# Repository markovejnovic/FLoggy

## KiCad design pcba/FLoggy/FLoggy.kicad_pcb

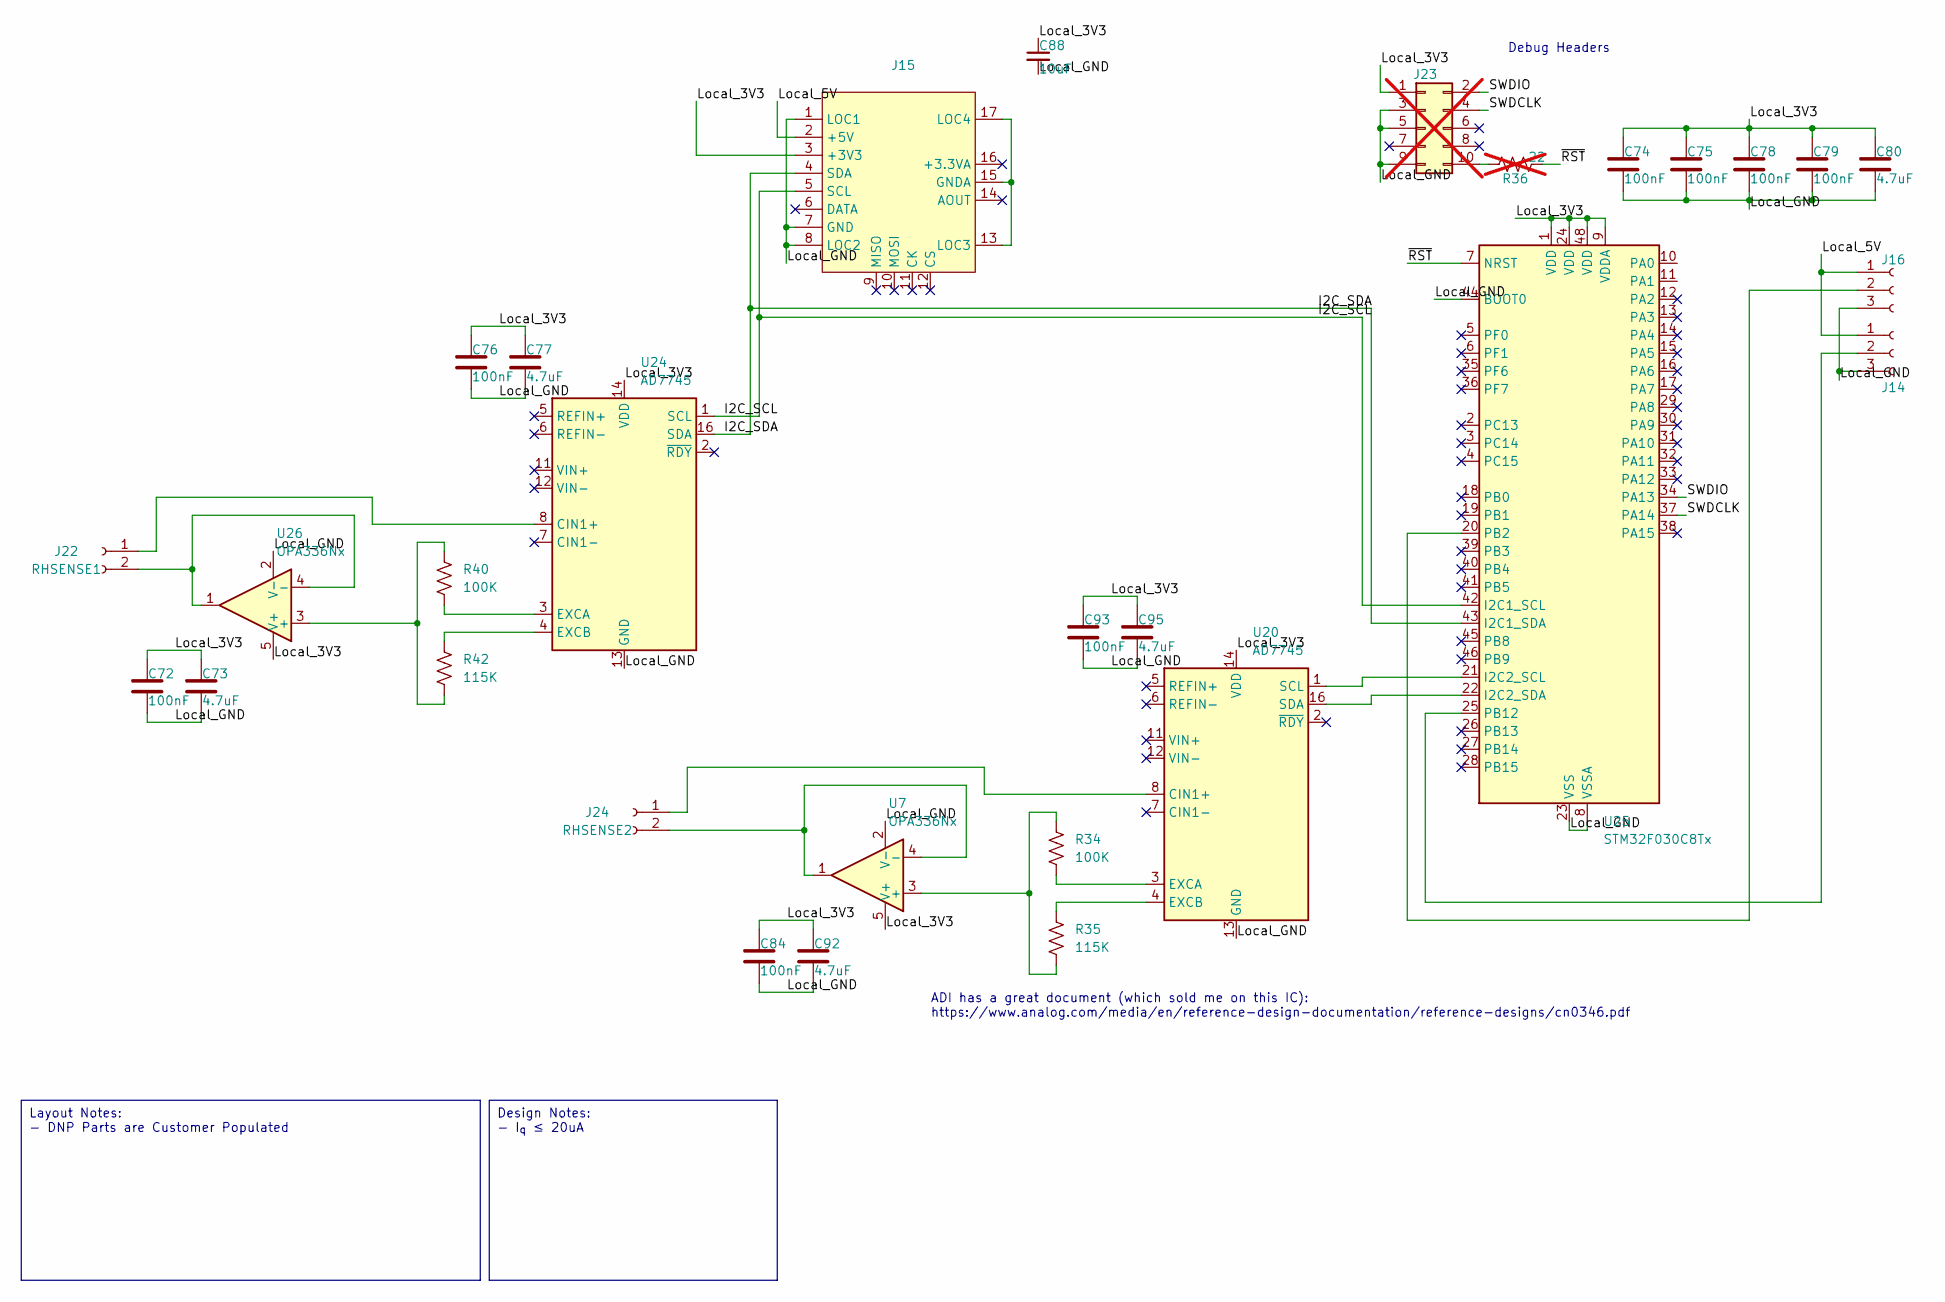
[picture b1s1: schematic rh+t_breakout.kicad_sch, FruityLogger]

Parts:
C72, C74, C75, C76, C78, C79, C84, C93: 100nF; C_0603_1608Metric; JLCPCB Basic? True
C73, C77, C80, C92, C95: 4.7uF; C_0805_2012Metric; JLCPCB Basic? True
C88: 10uF; C_0805_2012Metric; JLCPCB Basic? True
J14, J16: Conn_01x03_Socket; TerminalBlock_Phoenix_PT-1,5-3-3.5-H_1x03_P3.50mm_Horizontal
J15: FloggyModuleShield
J22: RHSENSE1; TerminalBlock_Phoenix_MPT-0,5-2-2.54_1x02_P2.54mm_Horizontal
J23: CTX_DBG; PinHeader_2x05_P1.27mm_Vertical_SMD; not fitted
J24: RHSENSE2; TerminalBlock_Phoenix_MPT-0,5-2-2.54_1x02_P2.54mm_Horizontal
R34, R40: 100K; R_0805_2012Metric; JLCPCB Basic? True
R35, R42: 115K; R_0603_1608Metric; JLCPCB Basic? False
R36: 22; R_0805_2012Metric; JLCPCB Basic? True; not fitted
U7, U26: OPA336Nx; SOT-23-5; JLCPCB Basic? False
U20, U24: AD7745; TSSOP-16_4.4x5mm_P0.65mm; JLCPCB Basic? False
U25: STM32F030C8Tx; LQFP-48_7x7mm_P0.5mm; JLCPCB Basic? True

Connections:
/RH + Temp Breakout 1/I2C_SCL: J15.5 (SCL), U24.1 (SCL), U25.42 (I2C1_SCL)
/RH + Temp Breakout 1/I2C_SDA: J15.4 (SDA), U24.16 (SDA), U25.43 (I2C1_SDA)
/RH + Temp Breakout 1/Local_3V3: C72.1, C73.1, C74.1, C75.1, C76.1, C77.1, C78.1, C79.1, C80.1, C84.1, C88.1, C92.1, C93.1, C95.1, J15.3 (+3V3), J23.1, U7.5 (V+), U20.14 (VDD), U24.14 (VDD), U25.1 (VDD), U25.9 (VDDA), U25.24 (VDD), U25.48 (VDD), U26.5 (V+)
/RH + Temp Breakout 1/Local_5V: J14.1, J15.2 (+5V), J16.1
/RH + Temp Breakout 1/Local_GND: C72.2, C73.2, C74.2, C75.2, C76.2, C77.2, C78.2, C79.2, C80.2, C84.2, C88.2, C92.2, C93.2, C95.2, J14.3, J15.1 (LOC1), J15.7 (GND), J15.8 (LOC2), J16.3, J23.3, J23.5, J23.9, U7.2 (V-), U20.13 (GND), U24.13 (GND), U25.8 (VSSA), U25.23 (VSS), U25.44 (BOOT0), U25.47 (VSS), U26.2 (V-)
/RH + Temp Breakout 1/SWDCLK: J23.4, U25.37 (PA14)
/RH + Temp Breakout 1/SWDIO: J23.2, U25.34 (PA13)
/RH + Temp Breakout 1/~RST: R36.2, U25.7 (NRST)
unnamed: J14.2, U25.25 (PB12)
unnamed: J15.13 (LOC3), J15.15 (GNDA), J15.17 (LOC4)
unnamed: J16.2, U25.20 (PB2)
unnamed: J22.1, U24.8 (CIN1+)
unnamed: J22.2, U26.1, U26.4 (-)
unnamed: J23.10, R36.1
unnamed: J24.1, U20.8 (CIN1+)
unnamed: J24.2, U7.1, U7.4 (-)
unnamed: R34.1, R35.2, U7.3 (+)
unnamed: R34.2, U20.3 (EXCA)
unnamed: R35.1, U20.4 (EXCB)
unnamed: U20.1 (SCL), U25.21 (I2C2_SCL)
unnamed: U20.16 (SDA), U25.22 (I2C2_SDA)
unnamed: R40.2, U24.3 (EXCA)
unnamed: R42.1, U24.4 (EXCB)
unnamed: R40.1, R42.2, U26.3 (+)

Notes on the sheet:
Design Notes: - I_{q} ≤ 20uA
Layout Notes: - DNP Parts are Customer Populated
Debug Headers
ADI has a great document (which sold me on this IC): https://www.analog.com/media/en/reference-design-documentation/reference-designs/cn0346.pdf

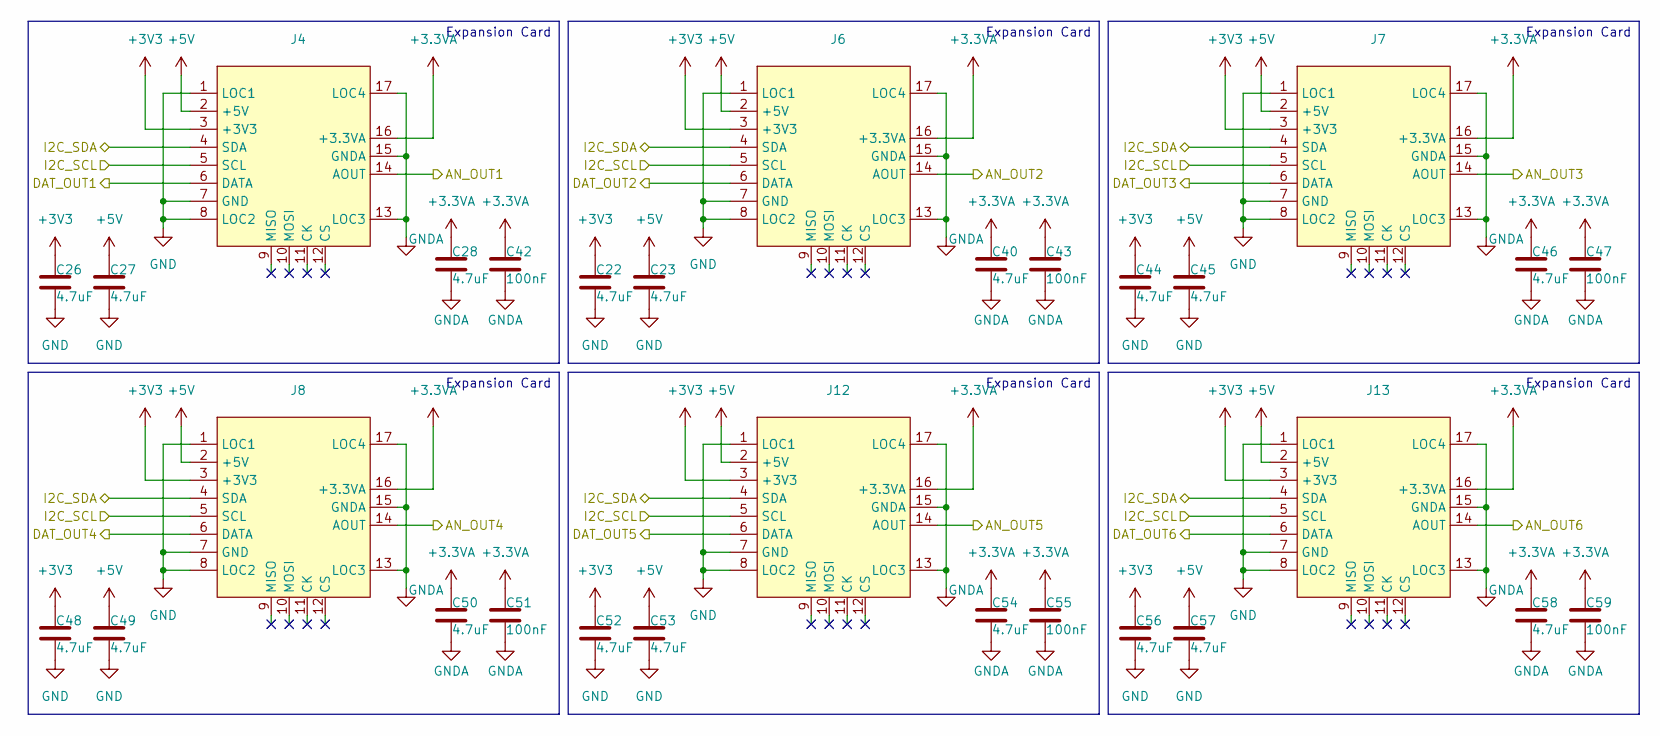
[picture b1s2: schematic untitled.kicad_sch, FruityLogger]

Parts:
C22, C23, C26, C27, C28, C40, C44, C45, C46, C48, C49, C50, C52, C53, C54, C56, C57, C58: 4.7uF; C_0805_2012Metric; JLCPCB Basic? True
C42, C43, C47, C51, C55, C59: 100nF; C_0603_1608Metric; JLCPCB Basic? True
J4, J6, J7, J8, J12, J13: FloggyModuleBase

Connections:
+3.3VA: C28.1, C40.1, C42.1, C43.1, C46.1, C47.1, C50.1, C51.1, C54.1, C55.1, C58.1, C59.1, J4.16 (+3.3VA), J6.16 (+3.3VA), J7.16 (+3.3VA), J8.16 (+3.3VA), J12.16 (+3.3VA), J13.16 (+3.3VA); also elsewhere on the board
+3V3: C22.1, C26.1, C44.1, C48.1, C52.1, C56.1, J4.3 (+3V3), J6.3 (+3V3), J7.3 (+3V3), J8.3 (+3V3), J12.3 (+3V3), J13.3 (+3V3); also elsewhere on the board
+5V: C23.1, C27.1, C45.1, C49.1, C53.1, C57.1, J4.2 (+5V), J6.2 (+5V), J7.2 (+5V), J8.2 (+5V), J12.2 (+5V), J13.2 (+5V); also elsewhere on the board
/MicroController/AIN1: J4.14 (AOUT); also elsewhere on the board
/MicroController/AIN2: J6.14 (AOUT); also elsewhere on the board
/MicroController/AIN3: J7.14 (AOUT); also elsewhere on the board
/MicroController/AIN4: J8.14 (AOUT); also elsewhere on the board
/MicroController/AIN5: J12.14 (AOUT); also elsewhere on the board
/MicroController/AIN6: J13.14 (AOUT); also elsewhere on the board
/MicroController/GPIO1: J4.6 (DATA); also elsewhere on the board
/MicroController/GPIO2: J6.6 (DATA); also elsewhere on the board
/MicroController/GPIO3: J7.6 (DATA); also elsewhere on the board
/MicroController/GPIO4: J8.6 (DATA); also elsewhere on the board
/MicroController/GPIO5: J12.6 (DATA); also elsewhere on the board
/MicroController/GPIO6: J13.6 (DATA); also elsewhere on the board
/MicroController/SCL: J4.5 (SCL), J6.5 (SCL), J7.5 (SCL), J8.5 (SCL), J12.5 (SCL), J13.5 (SCL); also elsewhere on the board
/MicroController/SDA: J4.4 (SDA), J6.4 (SDA), J7.4 (SDA), J8.4 (SDA), J12.4 (SDA), J13.4 (SDA); also elsewhere on the board
GND: C22.2, C23.2, C26.2, C27.2, C44.2, C45.2, C48.2, C49.2, C52.2, C53.2, C56.2, C57.2, J4.1 (LOC1), J4.7 (GND), J4.8 (LOC2), J6.1 (LOC1), J6.7 (GND), J6.8 (LOC2), J7.1 (LOC1), J7.7 (GND), J7.8 (LOC2), J8.1 (LOC1), J8.7 (GND), J8.8 (LOC2), J12.1 (LOC1), J12.7 (GND), J12.8 (LOC2), J13.1 (LOC1), J13.7 (GND), J13.8 (LOC2); also elsewhere on the board
GNDA: C28.2, C40.2, C42.2, C43.2, C46.2, C47.2, C50.2, C51.2, C54.2, C55.2, C58.2, C59.2, J4.13 (LOC3), J4.15 (GNDA), J4.17 (LOC4), J6.13 (LOC3), J6.15 (GNDA), J6.17 (LOC4), J7.13 (LOC3), J7.15 (GNDA), J7.17 (LOC4), J8.13 (LOC3), J8.15 (GNDA), J8.17 (LOC4), J12.13 (LOC3), J12.15 (GNDA), J12.17 (LOC4), J13.13 (LOC3), J13.15 (GNDA), J13.17 (LOC4); also elsewhere on the board

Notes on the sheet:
Expansion Card

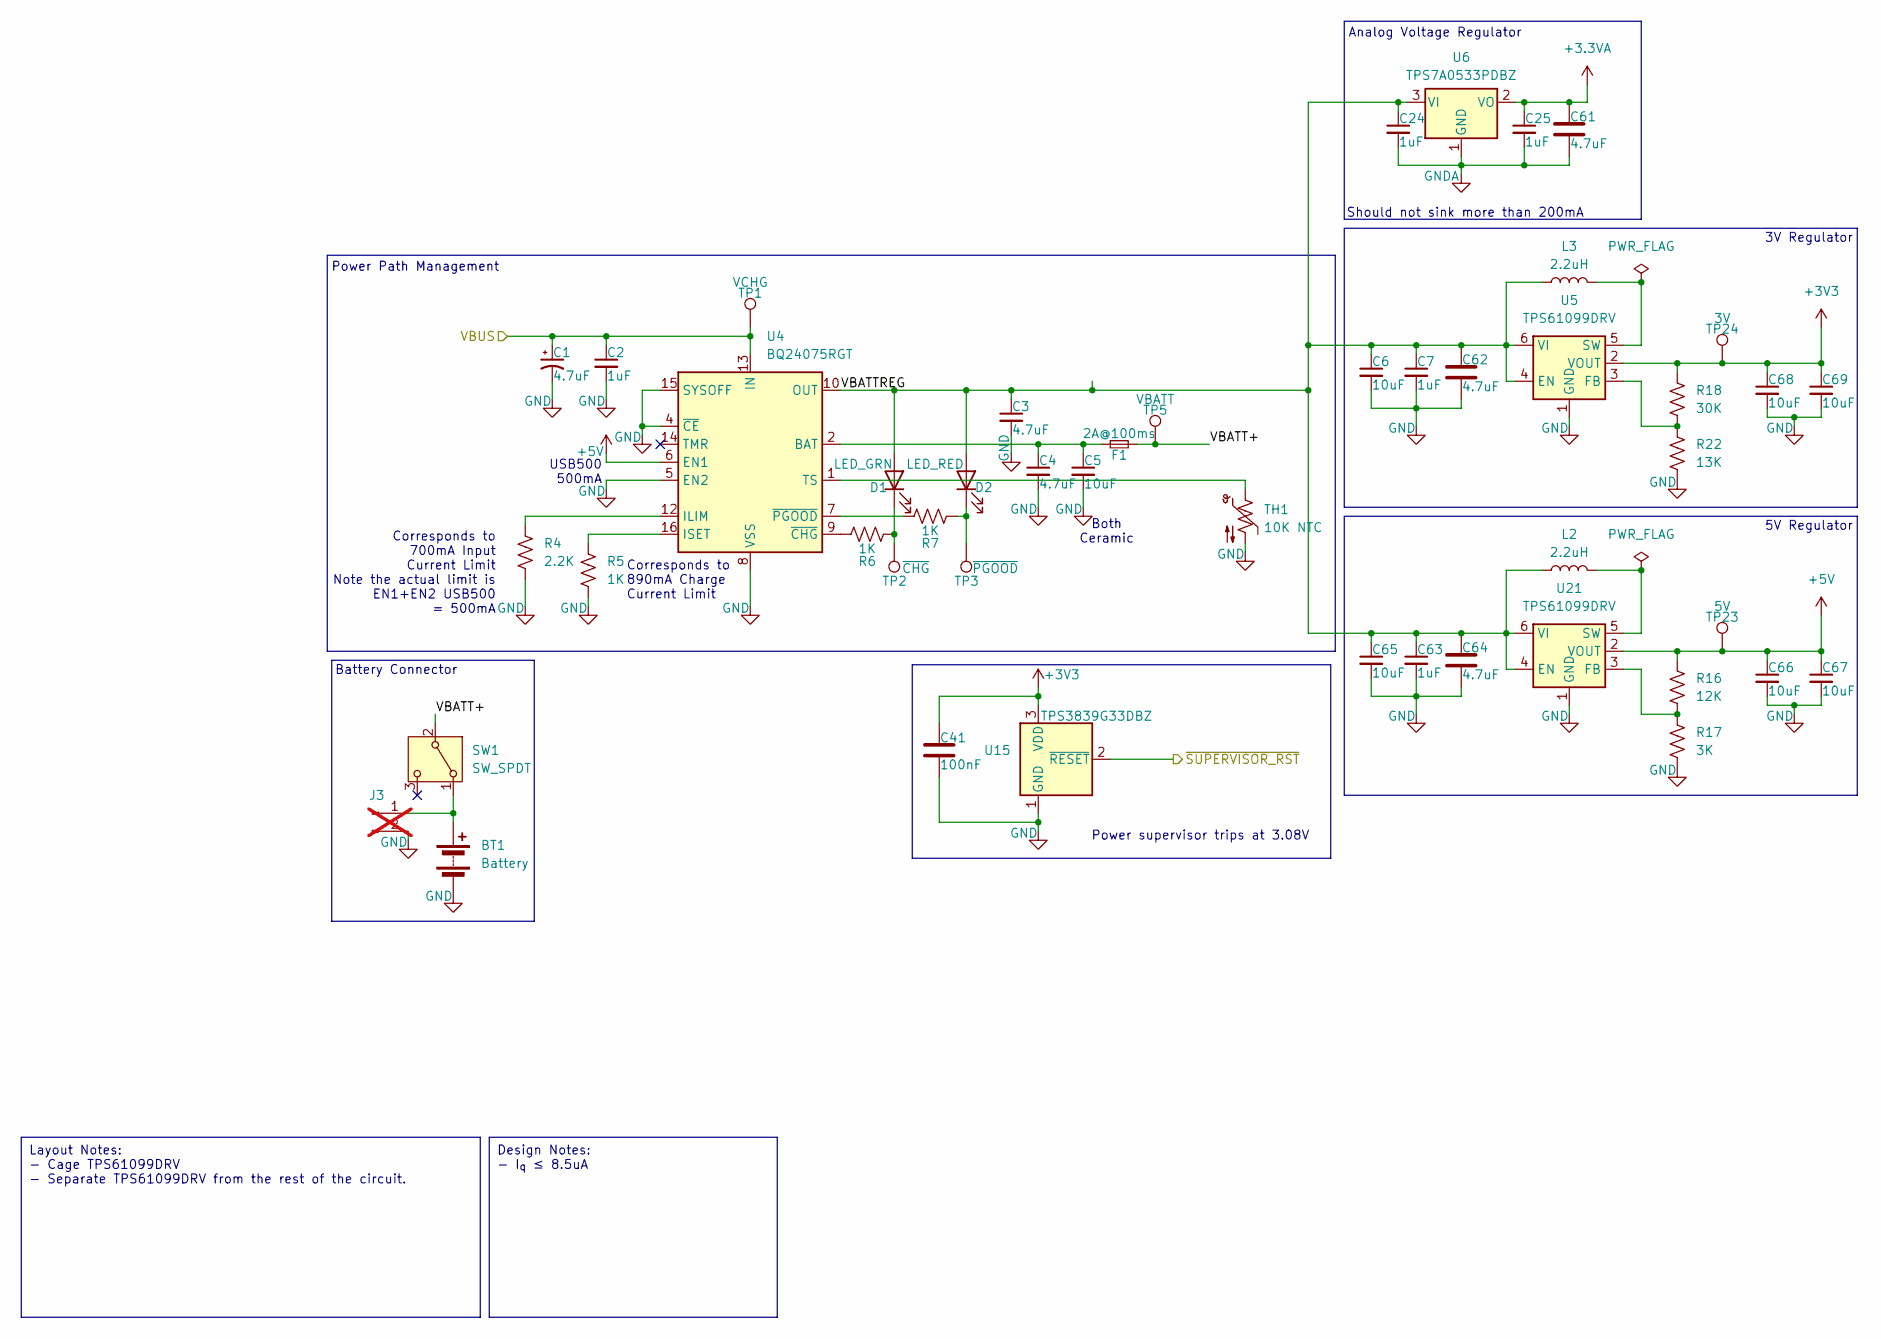
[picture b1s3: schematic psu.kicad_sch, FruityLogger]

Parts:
BT1: Battery; JST_PH_S2B-PH-K_1x02_P2.00mm_Horizontal; JLCPCB Basic? False
C1, C3, C4, C61, C62, C64: 4.7uF; C_0805_2012Metric; JLCPCB Basic? True
C2, C7, C24, C25, C63: 1uF; C_0805_2012Metric; JLCPCB Basic? True
C5, C6, C65, C66, C67, C68, C69: 10uF; C_0805_2012Metric; JLCPCB Basic? True
C41: 100nF; C_0603_1608Metric; JLCPCB Basic? True
D1: LED_GRN; LED_0805_2012Metric; JLCPCB Basic? True
D2: LED_RED; LED_0805_2012Metric; JLCPCB Basic? True
F1: 2A@100ms; FuseLine
J3: Conn_01x02_Pin; PinHeader_1x02_P2.54mm_Vertical; not fitted
L2, L3: 2.2uH; L_Sunlord_SWPA3015S; JLCPCB Basic? True
R4: 2.2K; R_0603_1608Metric; JLCPCB Basic? True
R5, R6, R7: 1K; R_0603_1608Metric; JLCPCB Basic? True
R16: 12K; R_0805_2012Metric; JLCPCB Basic? True
R17: 3K; R_0805_2012Metric; JLCPCB Basic? True
R18: 30K; R_0805_2012Metric; JLCPCB Basic? True
R22: 13K; R_0603_1608Metric; JLCPCB Basic? True
SW1: SW_SPDT; SW_Slide_SPDT_Angled_CK_OS102011MA1Q
TH1: 10K NTC; R_0603_1608Metric; JLCPCB Basic? False
TP1: VCHG; TestPoint_Pad_D1.0mm
TP2: ~{CHG}; TestPoint_Pad_D1.0mm
TP3: ~{PGOOD}; TestPoint_Pad_D1.0mm
TP5: VBATT; TestPoint_Pad_D1.0mm
TP23: 5V; TestPoint_Pad_D1.0mm
TP24: 3V; TestPoint_Pad_D1.0mm
U4: BQ24075RGT; VQFN-16-1EP_3x3mm_P0.5mm_EP1.6x1.6mm; JLCPCB Basic? False
U5, U21: TPS61099DRV; WSON-6-1EP_2x2mm_P0.65mm_EP1x1.6mm; JLCPCB Basic? False
U6: TPS7A0533PDBZ; SOT-23; JLCPCB Basic? False
U15: TPS3839G33DBZ; SOT-23; JLCPCB Basic? False

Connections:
+3.3VA: C25.1, C61.1, U6.2 (VO); also elsewhere on the board
+3V3: C41.1, C68.1, C69.1, R18.1, TP24.1, U5.2 (VOUT), U15.3 (VDD); also elsewhere on the board
+5V: C66.1, C67.1, R16.1, TP23.1, U4.6 (EN1), U21.2 (VOUT); also elsewhere on the board
/MicroController/~RST: U15.2 (~RESET); also elsewhere on the board
/Power Supply/VBATT+: F1.2, SW1.2 (B), TP5.1
/Power Supply/VBATTREG: C3.1, C6.1, C7.1, C24.1, C62.1, C63.1, C64.1, C65.1, D1.2 (A), D2.2 (A), L2.1, L3.1, U4.10 (OUT), U4.11 (OUT), U5.4 (EN), U5.6 (VI), U6.3 (VI), U21.4 (EN), U21.6 (VI)
GND: BT1.2 (-), C1.2, C2.2, C3.2, C4.2, C5.2, C6.2, C7.2, C41.2, C62.2, C63.2, C64.2, C65.2, C66.2, C67.2, C68.2, C69.2, J3.2, R4.2, R5.2, R17.2, R22.2, TH1.2, U4.4 (~CE), U4.5 (EN2), U4.8 (VSS), U4.15 (SYSOFF), U4.17 (VSS), U5.1 (GND), U5.7 (GND), U15.1 (GND), U21.1 (GND), U21.7 (GND); also elsewhere on the board
GNDA: C24.2, C25.2, C61.2, U6.1 (GND); also elsewhere on the board
unnamed: BT1.1 (+), J3.1, SW1.1 (A)
unnamed: C4.1, C5.1, F1.1, U4.2 (BAT), U4.3 (BAT)
unnamed: D1.1 (K), R6.2, TP2.1
unnamed: D2.1 (K), R7.1, TP3.1
unnamed: R4.1, U4.12 (ILIM)
unnamed: R5.1, U4.16 (ISET)
unnamed: TH1.1, U4.1 (TS)
unnamed: R6.1, U4.9 (~CHG)
unnamed: R7.2, U4.7 (~PGOOD)
unnamed: R18.2, R22.1, U5.3 (FB)
unnamed: L3.2, U5.5 (SW)
unnamed: R16.2, R17.1, U21.3 (FB)
unnamed: L2.2, U21.5 (SW)
VBUS: C1.1, C2.1, TP1.1, U4.13 (IN); also elsewhere on the board

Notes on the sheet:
Layout Notes: - Cage TPS61099DRV - Separate TPS61099DRV from the rest of the circuit.
Design Notes: - I_{q} ≤ 8.5uA
Analog Voltage Regulator
5V Regulator
3V Regulator
Should not sink more than 200mA
Corresponds to 890mA Charge Current Limit
USB500 500mA
Battery Connector
Corresponds to 700mA Input Current Limit Note the actual limit is EN1+EN2 USB500 = 500mA
Both Ceramic
Power Path Management
Power supervisor trips at 3.08V

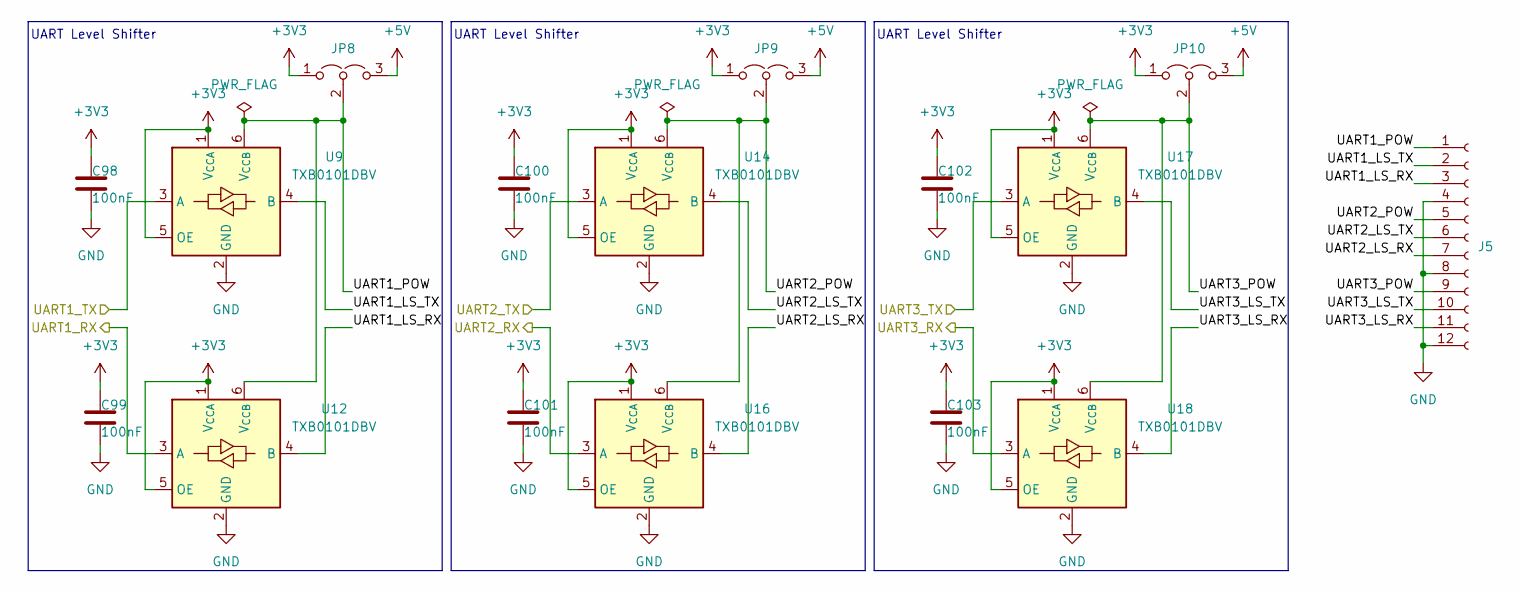
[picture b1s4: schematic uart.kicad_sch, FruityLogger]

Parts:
C98, C99, C100, C101, C102, C103: 100nF; C_0603_1608Metric; JLCPCB Basic? True
J5: Conn_01x12_Socket; TerminalBlock_TE_1-282834-2_1x12_P2.54mm_Horizontal
JP8, JP9, JP10: Jumper_3_Open; PinHeader_1x03_P2.54mm_Vertical
U9, U12, U14, U16, U17, U18: TXB0101DBV; SOT-23-6

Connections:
+3V3: C98.1, C99.1, C100.1, C101.1, C102.1, C103.1, JP8.1 (A), JP9.1 (A), JP10.1 (A), U9.1 (V_{CCA}), U9.5 (OE), U12.1 (V_{CCA}), U12.5 (OE), U14.1 (V_{CCA}), U14.5 (OE), U16.1 (V_{CCA}), U16.5 (OE), U17.1 (V_{CCA}), U17.5 (OE), U18.1 (V_{CCA}), U18.5 (OE); also elsewhere on the board
+5V: JP8.3 (B), JP9.3 (B), JP10.3 (B); also elsewhere on the board
/MicroController/UART3V3_1_RX: U18.3 (A); also elsewhere on the board
/MicroController/UART3V3_1_TX: U17.3 (A); also elsewhere on the board
/MicroController/UART3V3_2_RX: U16.3 (A); also elsewhere on the board
/MicroController/UART3V3_2_TX: U14.3 (A); also elsewhere on the board
/MicroController/UART3V3_3_RX: U12.3 (A); also elsewhere on the board
/MicroController/UART3V3_3_TX: U9.3 (A); also elsewhere on the board
/UART Peripherals/UART1_LS_RX: J5.3, U12.4 (B)
/UART Peripherals/UART1_LS_TX: J5.2, U9.4 (B)
/UART Peripherals/UART1_POW: J5.1, JP8.2 (C), U9.6 (V_{CCB}), U12.6 (V_{CCB})
/UART Peripherals/UART2_LS_RX: J5.7, U16.4 (B)
/UART Peripherals/UART2_LS_TX: J5.6, U14.4 (B)
/UART Peripherals/UART2_POW: J5.5, JP9.2 (C), U14.6 (V_{CCB}), U16.6 (V_{CCB})
/UART Peripherals/UART3_LS_RX: J5.11, U18.4 (B)
/UART Peripherals/UART3_LS_TX: J5.10, U17.4 (B)
/UART Peripherals/UART3_POW: J5.9, JP10.2 (C), U17.6 (V_{CCB}), U18.6 (V_{CCB})
GND: C98.2, C99.2, C100.2, C101.2, C102.2, C103.2, J5.4, J5.8, J5.12, U9.2 (GND), U12.2 (GND), U14.2 (GND), U16.2 (GND), U17.2 (GND), U18.2 (GND); also elsewhere on the board

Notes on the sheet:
UART Level Shifter

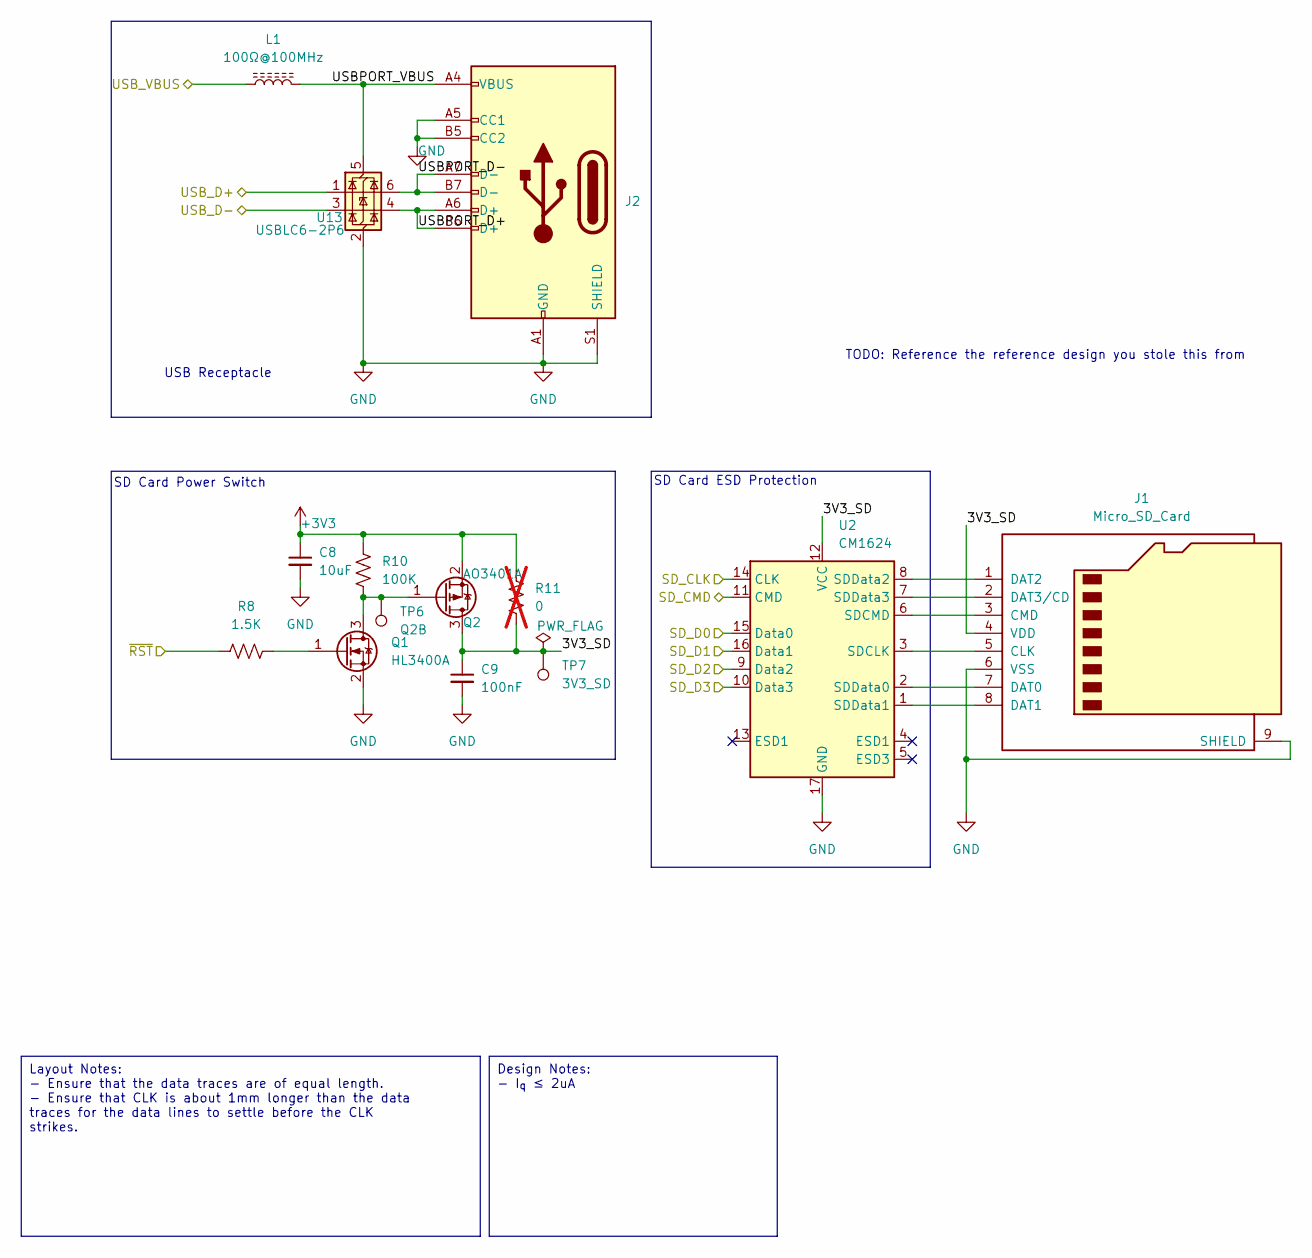
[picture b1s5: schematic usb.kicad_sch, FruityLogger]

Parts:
C8: 10uF; C_0805_2012Metric; JLCPCB Basic? True
C9: 100nF; C_0603_1608Metric; JLCPCB Basic? True
J1: Micro_SD_Card; microSD_HC_Hirose_DM3AT-SF-PEJM5; JLCPCB Basic? False
J2: USB_C_Receptacle_USB2.0_14P; USB_C_Receptacle_Amphenol_12401610E4-2A; JLCPCB Basic? False
L1: 100Ω@100MHz; L_0805_2012Metric; JLCPCB Basic? True
Q1: HL3400A; SOT-23; JLCPCB Basic? True
Q2: AO3401A; SOT-23; JLCPCB Basic? True
R8: 1.5K; R_0603_1608Metric; JLCPCB Basic? True
R10: 100K; R_0603_1608Metric; JLCPCB Basic? True
R11: 0; R_1206_3216Metric; JLCPCB Basic? True; not fitted
TP6: Q2B; TestPoint_Pad_D1.0mm
TP7: 3V3_SD; TestPoint_Pad_D1.0mm
U2: CM1624; OnSemi_UDFN-16-1EP_1.35x3.3mm_P0.4mm_EP0.4x2.8mm; JLCPCB Basic? False
U13: USBLC6-2P6; SOT-666; JLCPCB Basic? False

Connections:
+3V3: C8.1, Q2.2 (S), R10.2, R11.2; also elsewhere on the board
/MicroController/SDIO_CK: U2.14 (CLK); also elsewhere on the board
/MicroController/SDIO_CMD: U2.11 (CMD); also elsewhere on the board
/MicroController/SDIO_D0: U2.15 (Data0); also elsewhere on the board
/MicroController/USB_D+: U13.1 (I/O1); also elsewhere on the board
/MicroController/USB_D-: U13.3 (I/O2); also elsewhere on the board
/MicroController/~RST: R8.1; also elsewhere on the board
/Peripheral Connectors/3V3_SD: C9.1, J1.4 (VDD), Q2.3 (D), R11.1, TP7.1, U2.12 (VCC)
/Peripheral Connectors/SD_D1: U2.16 (Data1)
/Peripheral Connectors/SD_D2: U2.9 (Data2)
/Peripheral Connectors/SD_D3: U2.10 (Data3)
/Peripheral Connectors/USBPORT_D+: J2.A6 (D+), J2.B6 (D+), U13.4 (I/O2)
/Peripheral Connectors/USBPORT_D-: J2.A7 (D-), J2.B7 (D-), U13.6 (I/O1)
/Peripheral Connectors/USBPORT_VBUS: J2.A4 (VBUS), J2.A9 (VBUS), J2.B4 (VBUS), J2.B9 (VBUS), L1.2, U13.5 (VBUS)
GND: C8.2, C9.2, J1.6 (VSS), J1.9 (SHIELD), J2.A1 (GND), J2.A5 (CC1), J2.A12 (GND), J2.B1 (GND), J2.B5 (CC2), J2.B12 (GND), J2.S1 (SHIELD), Q1.2 (S), U2.17 (GND), U13.2 (GND); also elsewhere on the board
unnamed: J1.5 (CLK), U2.3 (SDCLK)
unnamed: J1.3 (CMD), U2.6 (SDCMD)
unnamed: J1.7 (DAT0), U2.2 (SDData0)
unnamed: J1.8 (DAT1), U2.1 (SDData1)
unnamed: J1.1 (DAT2), U2.8 (SDData2)
unnamed: J1.2 (DAT3/CD), U2.7 (SDData3)
unnamed: Q1.3 (D), Q2.1 (G), R10.1, TP6.1
unnamed: Q1.1 (G), R8.2
VBUS: L1.1; also elsewhere on the board

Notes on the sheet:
Layout Notes: - Ensure that the data traces are of equal length. - Ensure that CLK is about 1mm longer than the data traces for the data lines to settle before the CLK strikes.
Design Notes: - I_{q} ≤ 2uA
USB Receptacle
SD Card ESD Protection
TODO: Reference the reference design you stole this from
SD Card Power Switch

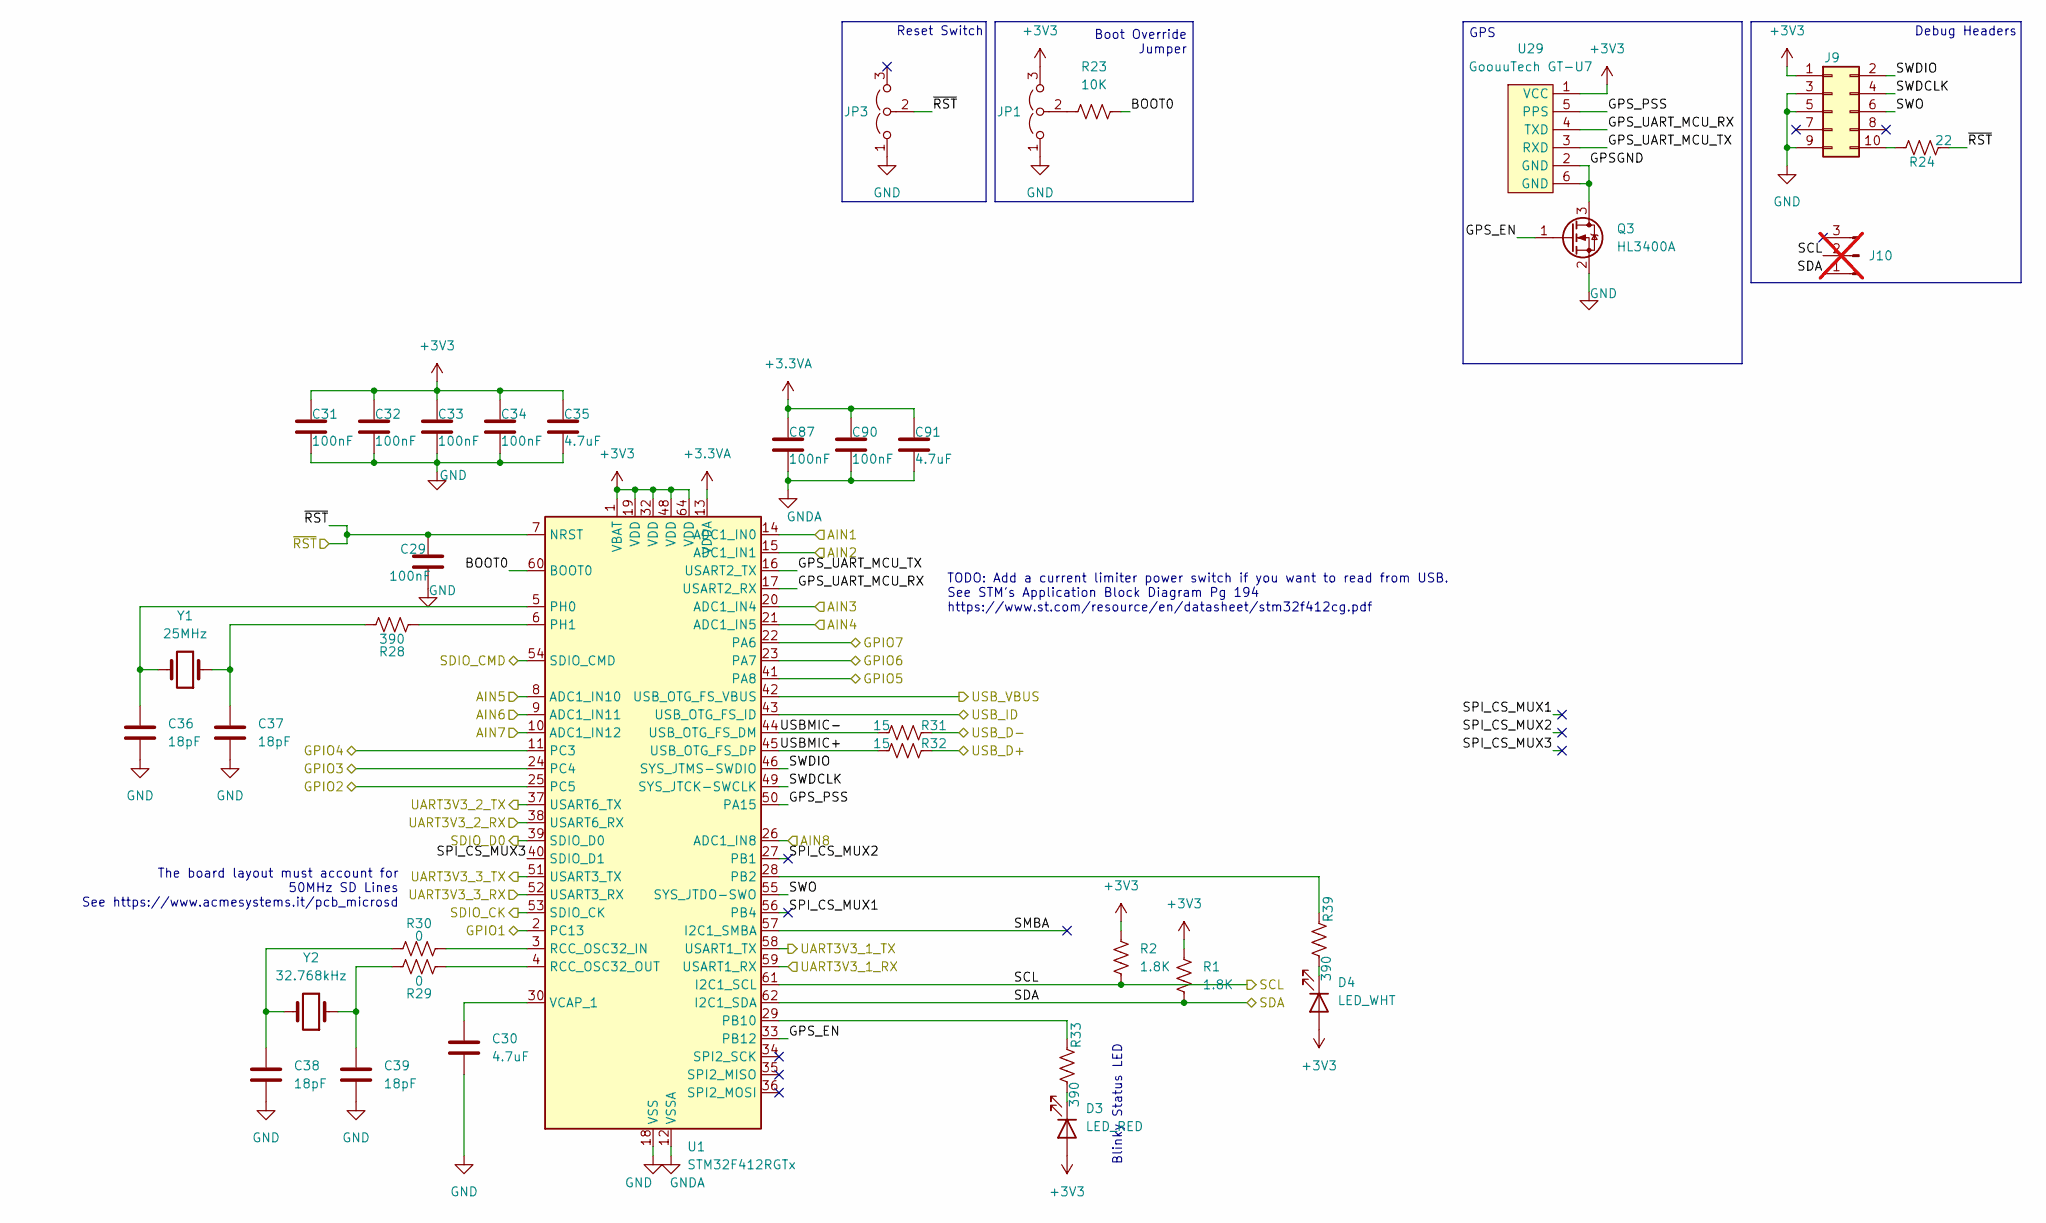
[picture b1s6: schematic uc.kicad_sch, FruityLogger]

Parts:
C29, C31, C32, C33, C34, C87, C90: 100nF; C_0603_1608Metric; JLCPCB Basic? True
C30, C35, C91: 4.7uF; C_0805_2012Metric; JLCPCB Basic? True
C36, C37, C38, C39: 18pF; C_0603_1608Metric; JLCPCB Basic? True
D3: LED_RED; LED_0805_2012Metric; JLCPCB Basic? True
D4: LED_WHT; LED_0603_1608Metric; JLCPCB Basic? True
J9: CTX_DBG; PinHeader_2x05_P1.27mm_Vertical_SMD
J10: Conn_01x03_Pin; PinHeader_1x03_P2.54mm_Vertical; not fitted
JP1, JP3: Jumper_3_Open; PinHeader_1x03_P2.54mm_Vertical
Q3: HL3400A; SOT-23; JLCPCB Basic? True
R1, R2: 1.8K; R_0603_1608Metric; JLCPCB Basic? True
R23: 10K; R_0603_1608Metric; JLCPCB Basic? True
R24: 22; R_0805_2012Metric; JLCPCB Basic? True
R28, R33, R39: 390; R_0603_1608Metric; JLCPCB Basic? True
R29, R30: 0; R_1206_3216Metric; JLCPCB Basic? True
R31, R32: 15; R_0805_2012Metric; JLCPCB Basic? True
U1: STM32F412RGTx; LQFP-64_10x10mm_P0.5mm
U29: GoouuTech GT-U7; GouuTech GT-U7
Y1: 25MHz; Crystal_SMD_3225-4Pin_3.2x2.5mm; JLCPCB Basic? True
Y2: 32.768kHz; Crystal_SMD_3215-2Pin_3.2x1.5mm; JLCPCB Basic? False

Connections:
+3.3VA: C87.1, C90.1, C91.1, U1.13 (VDDA); also elsewhere on the board
+3V3: C31.1, C32.1, C33.1, C34.1, C35.1, D3.2 (A), D4.2 (A), J9.1, JP1.3 (B), R1.1, R2.1, U1.1 (VBAT), U1.19 (VDD), U1.32 (VDD), U1.48 (VDD), U1.64 (VDD), U29.1 (VCC); also elsewhere on the board
/MicroController/AIN1: U1.14 (ADC1_IN0); also elsewhere on the board
/MicroController/AIN2: U1.15 (ADC1_IN1); also elsewhere on the board
/MicroController/AIN3: U1.20 (ADC1_IN4); also elsewhere on the board
/MicroController/AIN4: U1.21 (ADC1_IN5); also elsewhere on the board
/MicroController/AIN5: U1.8 (ADC1_IN10); also elsewhere on the board
/MicroController/AIN6: U1.9 (ADC1_IN11); also elsewhere on the board
/MicroController/AIN7: U1.10 (ADC1_IN12)
/MicroController/AIN8: U1.26 (ADC1_IN8)
/MicroController/BOOT0: R23.2, U1.60 (BOOT0)
/MicroController/GPIO1: U1.2 (PC13); also elsewhere on the board
/MicroController/GPIO2: U1.25 (PC5); also elsewhere on the board
/MicroController/GPIO3: U1.24 (PC4); also elsewhere on the board
/MicroController/GPIO4: U1.11 (PC3); also elsewhere on the board
/MicroController/GPIO5: U1.41 (PA8); also elsewhere on the board
/MicroController/GPIO6: U1.23 (PA7); also elsewhere on the board
/MicroController/GPIO7: U1.22 (PA6)
/MicroController/GPSGND: Q3.3 (D), U29.2 (GND), U29.6 (GND)
/MicroController/GPS_EN: Q3.1 (G), U1.33 (PB12)
/MicroController/GPS_PSS: U1.50 (PA15), U29.5 (PPS)
/MicroController/GPS_UART_MCU_RX: U1.17 (USART2_RX), U29.4 (TXD)
/MicroController/GPS_UART_MCU_TX: U1.16 (USART2_TX), U29.3 (RXD)
/MicroController/SCL: J10.2, R2.2, U1.61 (I2C1_SCL); also elsewhere on the board
/MicroController/SDA: J10.1, R1.2, U1.62 (I2C1_SDA); also elsewhere on the board
/MicroController/SDIO_CK: U1.53 (SDIO_CK); also elsewhere on the board
/MicroController/SDIO_CMD: U1.54 (SDIO_CMD); also elsewhere on the board
/MicroController/SDIO_D0: U1.39 (SDIO_D0); also elsewhere on the board
/MicroController/SMBA: U1.57 (I2C1_SMBA)
/MicroController/SPI_CS_MUX1: U1.56 (PB4)
/MicroController/SPI_CS_MUX2: U1.27 (PB1)
/MicroController/SPI_CS_MUX3: U1.40 (SDIO_D1)
/MicroController/SWDCLK: J9.4, U1.49 (SYS_JTCK-SWCLK)
/MicroController/SWDIO: J9.2, U1.46 (SYS_JTMS-SWDIO)
/MicroController/SWO: J9.6, U1.55 (SYS_JTDO-SWO)
/MicroController/UART3V3_1_RX: U1.59 (USART1_RX); also elsewhere on the board
/MicroController/UART3V3_1_TX: U1.58 (USART1_TX); also elsewhere on the board
/MicroController/UART3V3_2_RX: U1.38 (USART6_RX); also elsewhere on the board
/MicroController/UART3V3_2_TX: U1.37 (USART6_TX); also elsewhere on the board
/MicroController/UART3V3_3_RX: U1.52 (USART3_RX); also elsewhere on the board
/MicroController/UART3V3_3_TX: U1.51 (USART3_TX); also elsewhere on the board
/MicroController/USBMIC+: R32.2, U1.45 (USB_OTG_FS_DP)
/MicroController/USBMIC-: R31.2, U1.44 (USB_OTG_FS_DM)
/MicroController/USB_D+: R32.1; also elsewhere on the board
/MicroController/USB_D-: R31.1; also elsewhere on the board
/MicroController/USB_ID: U1.43 (USB_OTG_FS_ID)
/MicroController/~RST: C29.1, JP3.2 (C), R24.2, U1.7 (NRST); also elsewhere on the board
GND: C29.2, C30.2, C31.2, C32.2, C33.2, C34.2, C35.2, C36.2, C37.2, C38.2, C39.2, J9.3, J9.5, J9.9, JP1.1 (A), JP3.1 (A), Q3.2 (S), U1.18 (VSS), U1.31 (VSS), U1.47 (VSS), U1.63 (VSS); also elsewhere on the board
GNDA: C87.2, C90.2, C91.2, U1.12 (VSSA); also elsewhere on the board
unnamed: C37.1, R28.1, Y1.1
unnamed: C38.1, R30.1, Y2.2
unnamed: C39.1, R29.1, Y2.1
unnamed: D3.1 (K), R33.2
unnamed: D4.1 (K), R39.2
unnamed: J9.10, R24.1
unnamed: JP1.2 (C), R23.1
unnamed: R39.1, U1.28 (PB2)
unnamed: R33.1, U1.29 (PB10)
unnamed: R30.2, U1.3 (RCC_OSC32_IN)
unnamed: R29.2, U1.4 (RCC_OSC32_OUT)
unnamed: C36.1, U1.5 (PH0), Y1.2
unnamed: R28.2, U1.6 (PH1)
unnamed: C30.1, U1.30 (VCAP_1)
VBUS: U1.42 (USB_OTG_FS_VBUS); also elsewhere on the board

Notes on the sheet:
Blinky Status LED
TODO: Add a current limiter power switch if you want to read from USB. See STM's Application Block Diagram Pg 194 https://www.st.com/resource/en/datasheet/stm32f412cg.pdf
The board layout must account for 50MHz SD Lines See https://www.acmesystems.it/pcb_microsd
Boot Override Jumper
Reset Switch
Debug Headers
GPS
